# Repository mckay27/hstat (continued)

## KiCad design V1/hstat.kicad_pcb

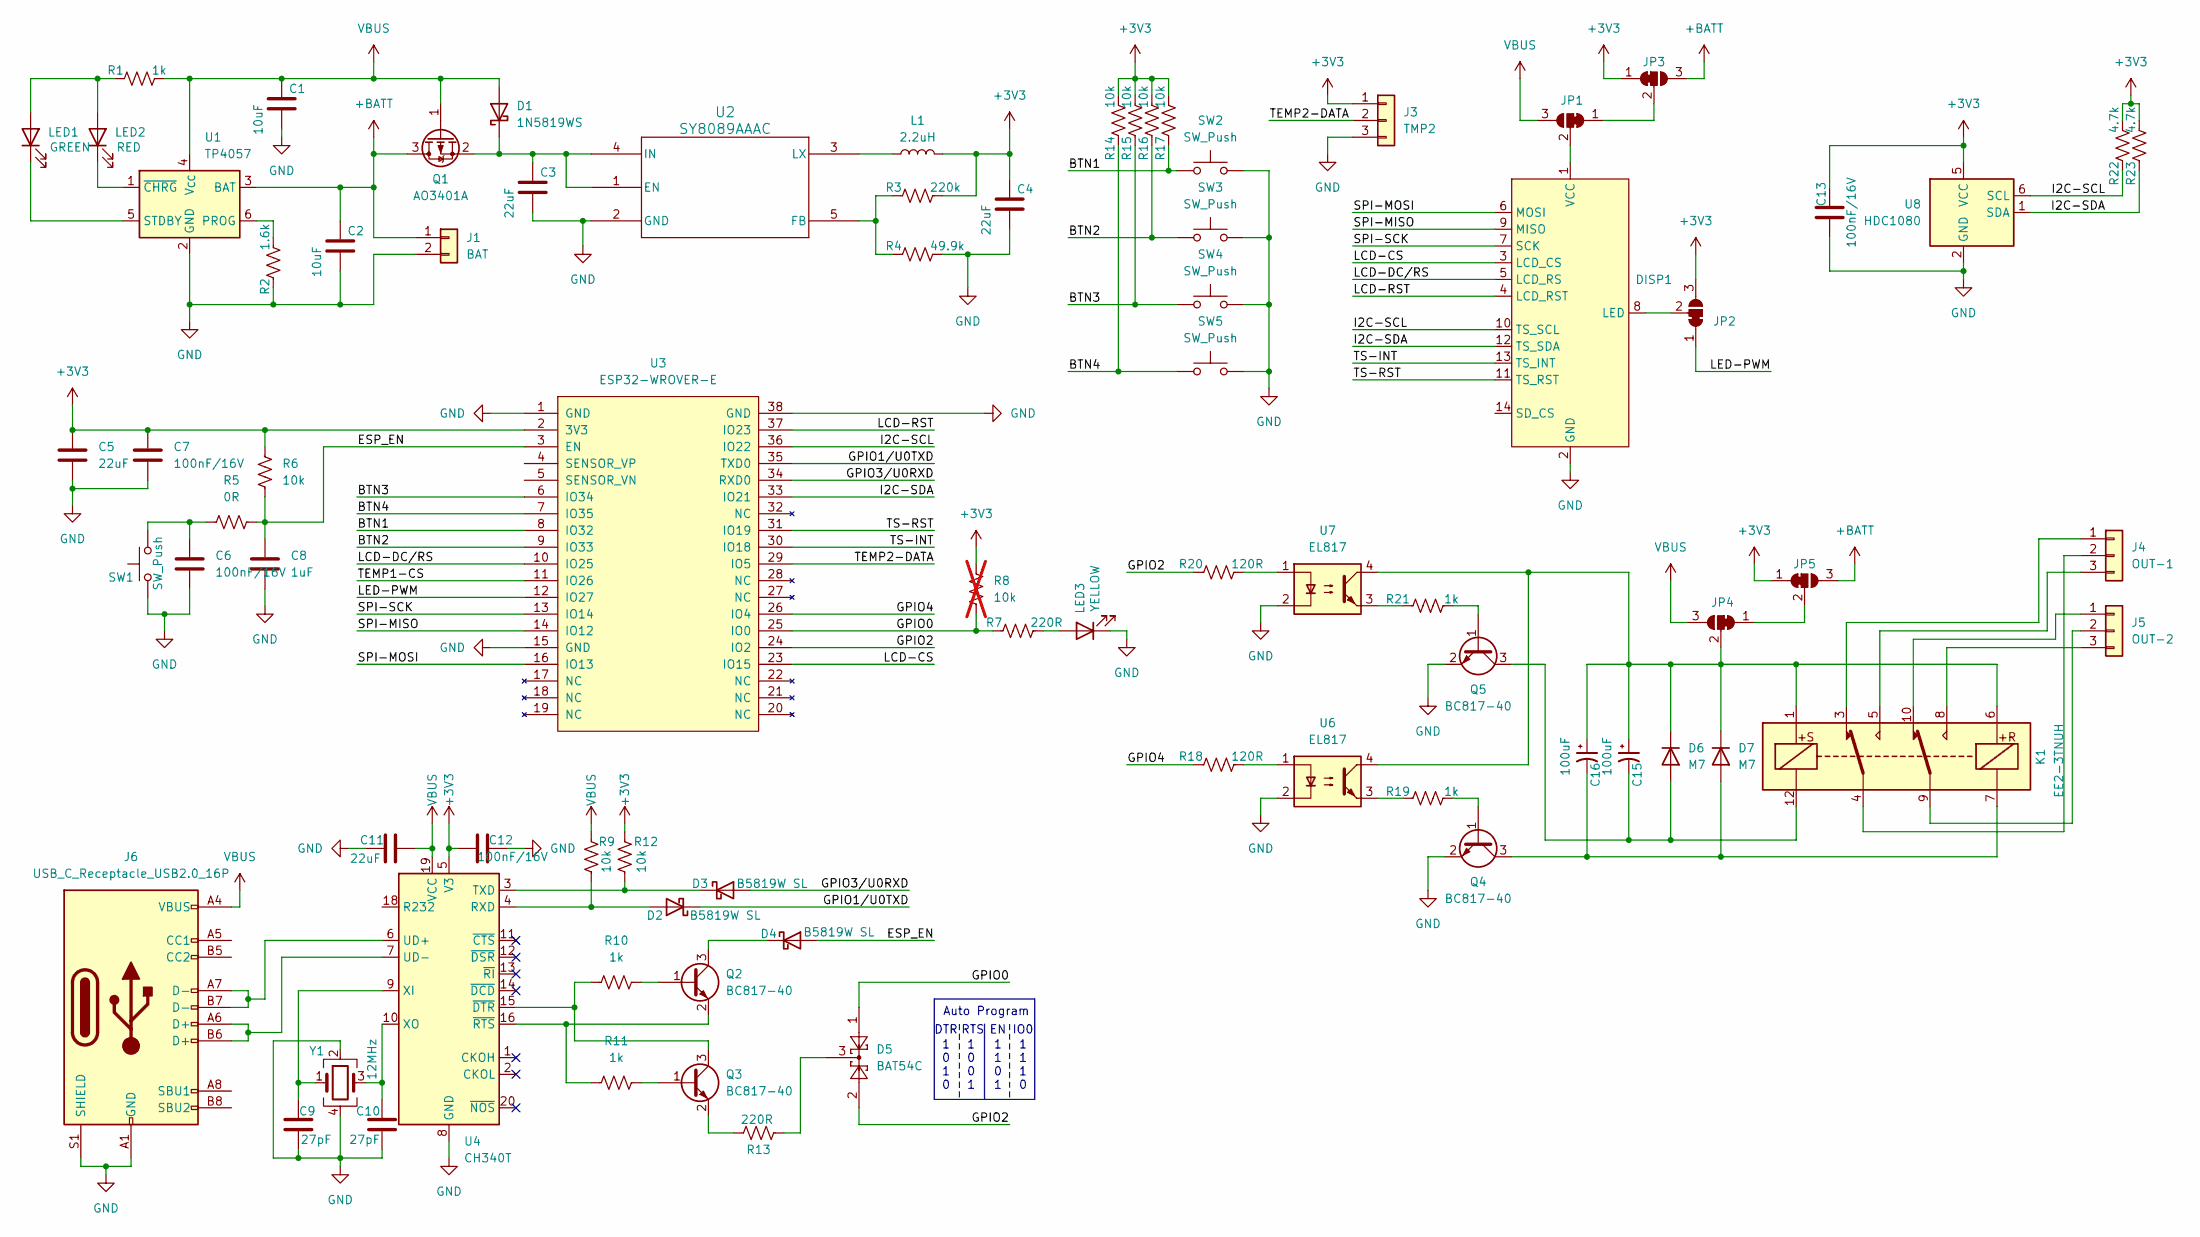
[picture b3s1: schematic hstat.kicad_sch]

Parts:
C1, C2: 10uF; C_0805_2012Metric; JLCPCB PN C15850
C3, C4, C5, C11: 22uF; C_0805_2012Metric; JLCPCB PN C45783
C6, C7, C12, C13: 100nF/16V; C_0805_2012Metric; JLCPCB PN C28233
C8: 1uF; C_0603_1608Metric; JLCPCB PN C15849
C9, C10: 27pF; C_0603_1608Metric; JLCPCB PN C107045
C15, C16: 100uF; CP_Elec_8x10; JLCPCB PN C116241
D1: 1N5819WS; D_SOD-323; JLCPCB PN C191023
D2, D3, D4: B5819W SL; D_SOD-123; JLCPCB PN C8598
D5: BAT54C; SOT-23; JLCPCB PN C37704
D6, D7: M7; D_SMA; JLCPCB PN C95872
DISP1: ST7796S-module
J1: BAT; JST_PH_B2B-PH-K_1x02_P2.00mm_Vertical
J3: TMP2; TerminalBlock_Phoenix_MKDS-1,5-3_1x03_P5.00mm_Horizontal
J4: OUT-1; TerminalBlock_Phoenix_MKDS-1,5-3_1x03_P5.00mm_Horizontal
J5: OUT-2; TerminalBlock_Phoenix_MKDS-1,5-3_1x03_P5.00mm_Horizontal
J6: USB_C_Receptacle_USB2.0_16P; USB_C_Receptacle_G-Switch_GT-USB-7010ASV
JP1, JP2, JP3, JP4, JP5: SolderJumper_3_Bridged12; SolderJumper-3_P1.3mm_Bridged12_RoundedPad1.0x1.5mm
K1: EE2-3TNUH; Relay_DPDT_Kemet_EE2_NUH_DoubleCoil
L1: 2.2uH; L_1008_2520Metric; JLCPCB PN C5832372
LED1: GREEN; LED_0805_2012Metric; JLCPCB PN C2297
LED2: RED; LED_0805_2012Metric; JLCPCB PN C84256
LED3: YELLOW; LED_0805_2012Metric; JLCPCB PN C2296
Q1: AO3401A; SOT-23; JLCPCB PN C15127
Q2, Q3, Q4, Q5: BC817-40; SOT-23; JLCPCB PN C20069155
R1, R10, R11, R19, R21: 1k; R_0805_2012Metric; JLCPCB PN C17513
R2: 1.6k; R_0805_2012Metric_Pad1.20x1.40mm_HandSolder
R3: 220k; R_0805_2012Metric; JLCPCB PN C17556
R4: 49.9k; R_0805_2012Metric; JLCPCB PN C17556
R5: 0R; R_0805_2012Metric; JLCPCB PN C17477
R6, R9, R12, R14, R15, R16, R17: 10k; R_0805_2012Metric; JLCPCB PN C17414
R7, R13: 220R; R_0805_2012Metric; JLCPCB PN C17557
R8: 10k; R_0805_2012Metric; not fitted
R18, R20: 120R; R_0805_2012Metric; JLCPCB PN C17557
R22, R23: 4.7k; R_0805_2012Metric; JLCPCB PN C17673
SW1, SW2, SW3, SW4, SW5: SW_Push; SW_Push_1P1T_XKB_TS-1187A; JLCPCB PN C318884
U1: TP4057; SOT-23-6; JLCPCB PN C12044
U2: SY8089AAAC; SY8089AAAC_SGY; JLCPCB PN C78988
U3: ESP32-WROVER-E; ESP32-WROVER-IE; JLCPCB PN C2973667
U4: CH340T; SSOP-20_5.3x7.2mm_P0.65mm; JLCPCB PN C8689
U6, U7: EL817; SMDIP-4_W9.53mm; JLCPCB PN C106900
U8: HDC1080; Texas_PWSON-N6; JLCPCB PN C82227
Y1: 12MHz; Crystal_SMD_3225-4Pin_3.2x2.5mm; JLCPCB PN C9002

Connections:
+3V3: C4.1, C5.1, C7.1, C12.1, C13.2, J3.1, JP2.3 (B), JP3.1 (A), JP5.1 (A), L1.2, R3.1, R6.1, R8.1, R12.2, R14.1, R15.1, R16.1, R17.1, R22.1, R23.1, U3.2 (3V3), U4.5 (V3), U8.5 (VCC)
+BATT: C2.1, J1.1, JP3.3 (B), JP5.3 (B), Q1.3 (D), U1.3 (BAT)
/BTN1: R17.2, SW2.1, U3.8 (IO32)
/BTN2: R16.2, SW3.1, U3.9 (IO33)
/BTN3: R15.2, SW4.1, U3.6 (IO34)
/BTN4: R14.2, SW5.1, U3.7 (IO35)
/ESP_EN: C8.1, D4.2 (A), R5.2, R6.2, U3.3 (EN)
/GPIO0: D5.1, R7.2, R8.2, U3.25 (IO0)
/GPIO1/U0TXD: D2.1 (K), U3.35 (TXD0)
/GPIO2: D5.2, R20.2, U3.24 (IO2)
/GPIO3/U0RXD: D3.2 (A), U3.34 (RXD0)
/GPIO4: R18.2, U3.26 (IO4)
/I2C-SCL: DISP1.10 (TS_SCL), R22.2, U3.36 (IO22), U8.6 (SCL)
/I2C-SDA: DISP1.12 (TS_SDA), R23.2, U3.33 (IO21), U8.1 (SDA)
/LCD-CS: DISP1.3 (LCD_CS), U3.23 (IO15)
/LCD-DC/RS: DISP1.5 (LCD_RS), U3.10 (IO25)
/LCD-RST: DISP1.4 (LCD_RST), U3.37 (IO23)
/LED-PWM: JP2.1 (A), U3.12 (IO27)
/SPI-MISO: DISP1.9 (MISO), U3.14 (IO12)
/SPI-MOSI: DISP1.6 (MOSI), U3.16 (IO13)
/SPI-SCK: DISP1.7 (SCK), U3.13 (IO14)
/TEMP1-CS: U3.11 (IO26)
/TEMP2-DATA: J3.2, U3.29 (IO5)
/TS-INT: DISP1.13 (TS_INT), U3.30 (IO18)
/TS-RST: DISP1.11 (TS_RST), U3.31 (IO19)
GND: C1.2, C2.2, C3.2, C4.2, C5.2, C6.2, C7.2, C8.2, C9.2, C10.2, C11.1, C12.2, C13.1, DISP1.2 (GND), J1.2, J3.3, J6.A1 (GND), J6.A12 (GND), J6.B1 (GND), J6.B12 (GND), J6.S1 (SHIELD), LED3.1 (K), Q4.2 (E), Q5.2 (E), R2.2, R4.1, SW1.1, SW2.2, SW3.2, SW4.2, SW5.2, U1.2 (GND), U2.2 (GND), U3.1 (GND), U3.15 (GND), U3.38 (GND), U4.8 (GND), U6.2, U7.2, U8.2 (GND), Y1.2, Y1.4
unnamed: C6.1, R5.1, SW1.2
unnamed: C3.1, D1.1 (K), Q1.2 (S), U2.1 (EN), U2.4 (IN)
unnamed: D2.2 (A), R9.1, U4.4 (RXD)
unnamed: D3.1 (K), R12.1, U4.3 (TXD)
unnamed: D4.1 (K), Q2.3 (C)
unnamed: D5.3, R13.2
unnamed: C15.2, D6.2 (A), K1.12, Q5.3 (C)
unnamed: C15.1, C16.1, D6.1 (K), D7.1 (K), JP4.2 (C), K1.1, K1.6, U6.4, U7.4
unnamed: C16.2, D7.2 (A), K1.7, Q4.3 (C)
unnamed: DISP1.8 (LED), JP2.2 (C)
unnamed: DISP1.1 (VCC), JP1.2 (C)
unnamed: J4.1, K1.3
unnamed: J4.2, K1.4
unnamed: J4.3, K1.5
unnamed: J5.1, K1.10
unnamed: J5.2, K1.9
unnamed: J5.3, K1.8
unnamed: JP1.1 (A), JP3.2 (C)
unnamed: JP4.1 (A), JP5.2 (C)
unnamed: LED1.2 (A), LED2.2 (A), R1.2
unnamed: LED1.1 (K), U1.5 (STDBY)
unnamed: LED2.1 (K), U1.1 (~CHRG)
unnamed: LED3.2 (A), R7.1
unnamed: Q2.1 (B), R10.2
unnamed: Q2.2 (E), R11.1, U4.16 (~RTS)
unnamed: Q3.1 (B), R11.2
unnamed: Q3.3 (C), R10.1, U4.15 (~DTR)
unnamed: Q3.2 (E), R13.1
unnamed: Q4.1 (B), R19.2
unnamed: Q5.1 (B), R21.2
unnamed: R18.1, U6.1
unnamed: R19.1, U6.3
unnamed: R20.1, U7.1
unnamed: R21.1, U7.3
unnamed: R2.1, U1.6 (PROG)
unnamed: R3.2, R4.2, U2.5 (FB)
unnamed: L1.1, U2.3 (LX)
unnamed: J6.A7 (D-), J6.B7 (D-), U4.6 (UD+)
unnamed: J6.A6 (D+), J6.B6 (D+), U4.7 (UD-)
unnamed: C9.1, U4.9 (XI), Y1.1
unnamed: C10.1, U4.10 (XO), Y1.3
VBUS: C1.1, C11.2, D1.2 (A), J6.A4 (VBUS), J6.A9 (VBUS), J6.B4 (VBUS), J6.B9 (VBUS), JP1.3 (B), JP4.3 (B), Q1.1 (G), R1.1, R9.2, U1.4 (V_{CC}), U4.19 (VCC)

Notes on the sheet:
1 1 1 0
Auto Program
RTS
1 1 0 1
1 0 0 1
1 0 1 0
DTR
IO0

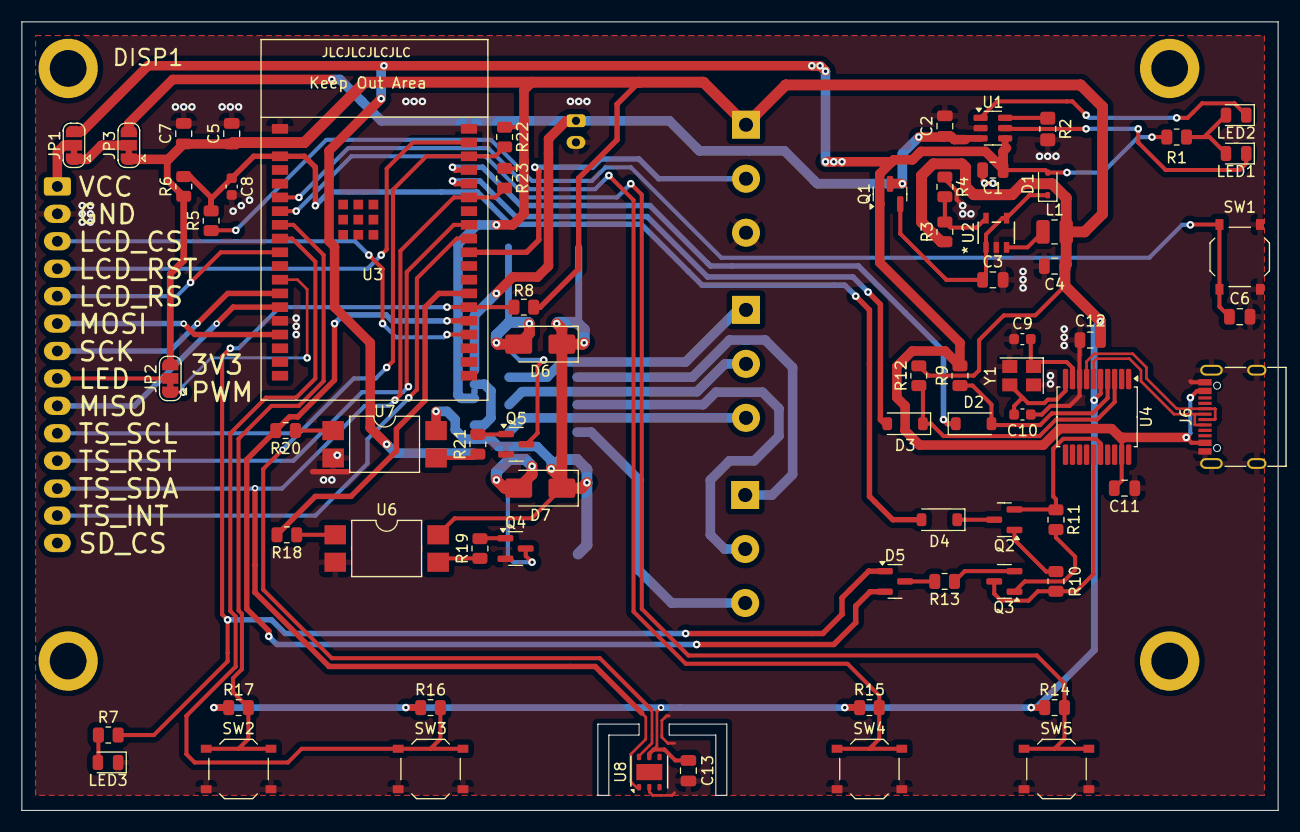
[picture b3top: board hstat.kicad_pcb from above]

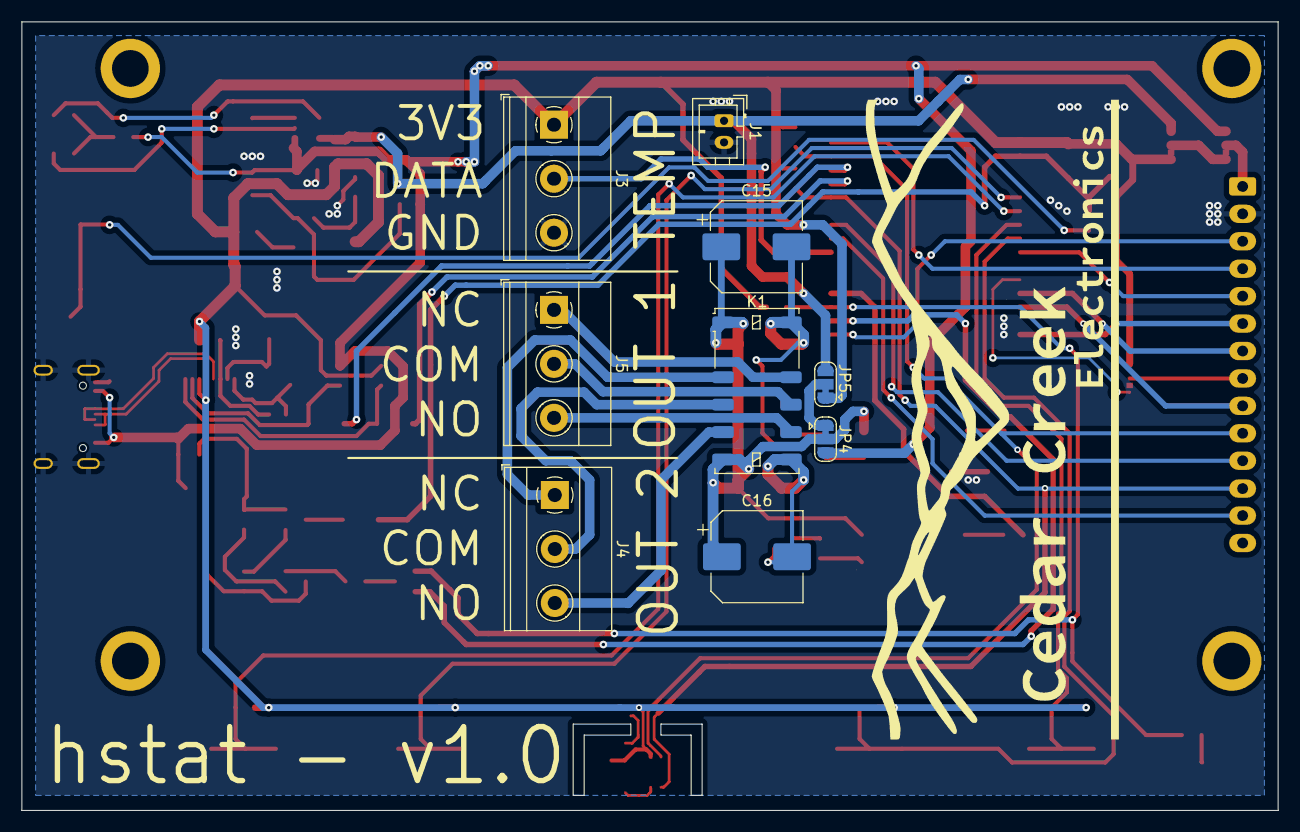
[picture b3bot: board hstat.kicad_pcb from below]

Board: 2 copper layers, 116.3 x 73.0 mm, 79 parts (9 on the bottom side), 67 nets.

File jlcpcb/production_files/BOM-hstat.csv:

Comment,Designator,Footprint,LCSC,Quantity
EL817,"U6,U7",SMDIP-4_W9.53mm,C106900,2
27pF,"C10,C9",C_0603_1608Metric,C107045,2
TP4057,U1,SOT-23-6,C12044,1
AO3401A,Q1,SOT-23,C15127,1
1uF,C8,C_0603_1608Metric,C15849,1
10uF,"C1,C2",C_0805_2012Metric,C15850,2
10k,"R12,R14,R15,R16,R17,R6,R9",R_0805_2012Metric,C17414,7
0R,R5,R_0805_2012Metric,C17477,1
1k,"R1,R10,R11,R19,R21",R_0805_2012Metric,C17513,5
220k,"R3,R4",R_0805_2012Metric,C17556,2
220R,"R13,R18,R20,R7",R_0805_2012Metric,C17557,4
4.7k,"R22,R23",R_0805_2012Metric,C17673,2
1N5819WS,D1,D_SOD-323,C191023,1
BC817-40,"Q2,Q3,Q4,Q5",SOT-23,C20069155,4
YELLOW,LED3,LED_0805_2012Metric,C2296,1
GREEN,LED1,LED_0805_2012Metric,C2297,1
100nF/16V,"C12,C13,C6,C7",C_0805_2012Metric,C28233,4
SW_Push,"SW1,SW2,SW3,SW4,SW5",SW_Push_1P1T_XKB_TS-1187A,C318884,5
BAT54C,D5,SOT-23,C37704,1
22uF,"C11,C3,C4,C5",C_0805_2012Metric,C45783,4
2.2uH,L1,L_1008_2520Metric,C5832372,1
SY8089AAAC,U2,SY8089AAAC_SGY,C78988,1
HDC1080,U8,Texas_PWSON-N6,C82227,1
RED,LED2,LED_0805_2012Metric,C84256,1
B5819W SL,"D2,D3,D4",D_SOD-123,C8598,3
CH340T,U4,SSOP-20_5.3x7.2mm_P0.65mm,C8689,1
12MHz,Y1,Crystal_SMD_3225-4Pin_3.2x2.5mm,C9002,1
M7,"D6,D7",D_SMA,C95872,2

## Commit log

2025-02-02 Add logos etc.
2025-02-02 new schematic
2025-02-02 v1.0
2025-02-02 v1.0 ordered
2025-03-23 Add comments
2025-03-24 Disable display timeout
2025-03-24 Comment out on_idle
2025-03-24 Fix Temperature Calibration Syntax
2025-03-25 Add Comment
2025-03-30 Change to Ext Temp + Misc Changes
2026-01-31 Move to V1 folder
2026-02-01 hstat dev in progress
2026-02-06 Before board split
2026-02-06 In progress
2026-02-07 Schematic tided up on display board
2026-02-07 Main board in progress
2026-02-07 Update kicad-lib
2026-02-08 Initial component placement done.
2026-02-08 Close stuff you dummy.
2026-02-08 Update library.
2026-02-11 Update lib
2026-02-11 Push progress
2026-02-12 Start layout
2026-02-13 Routing progress
2026-02-14 Schematic updates
2026-02-14 main board in good spot
2026-02-14 Display board in good spot
2026-02-14 Some more tweaks
2026-02-15 fix symbol
2026-02-15 Flip touch screen connector
2026-02-15 Finalize schematics
2026-02-15 Fixes
2026-02-15 Final updates
2026-02-15 Remove old single board
2026-02-15 Export 3d-models
2026-02-15 Add 3d-models
2026-02-15 Redo high voltage
2026-02-15 Close Kicad
2026-02-15 Update model
2026-02-15 Update 3d models
2026-02-15 Add LCSC part numbers
2026-02-16 Boards ordered
2026-02-26 Update connectors
2026-02-26 Update footprint
2026-02-28 More fixes
2026-04-03 Reorganize tree
2026-04-03 Move current SW to package
2026-04-03 First stab at status page
